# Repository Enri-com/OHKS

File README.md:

# Open-hardware knob system for acceleration control operations #

## Description

The hardware has been structured on a PCB where are mounted 9 keys and a mechanical encoder.
The keys are used to simulate, at the firmware level, the pressure of one keyboard button or a combination of them. 
Each key is equipped with anti-bounce circuitry and ade-quate ESD protection to prevent a malfunction or breakdown 
of the electronics.
The microcontroller is devoted to managing the USB HID communication. 
To have multiple options in terms of hardware solutions for the microcontroller, the PCB has been realized to be 
compatible with both ARM STM32 microcontroller and Teensy LC module.

## License

Copyright INFN-LNL 2020.
This documentation describes OHKS_WFP hardware and is licensed under the
CERN OHL v. 1.2.
You may redistribute and modify this documentation under the terms of the
CERN OHL v.1.2. (http://ohwr.org/cernohl). This documentation is distributed
WITHOUT ANY EXPRESS OR IMPLIED WARRANTY, INCLUDING OF
MERCHANTABILITY, SATISFACTORY QUALITY AND FITNESS FOR A
PARTICULAR PURPOSE. Please see the CERN OHL v.1.2 for applicable
conditions

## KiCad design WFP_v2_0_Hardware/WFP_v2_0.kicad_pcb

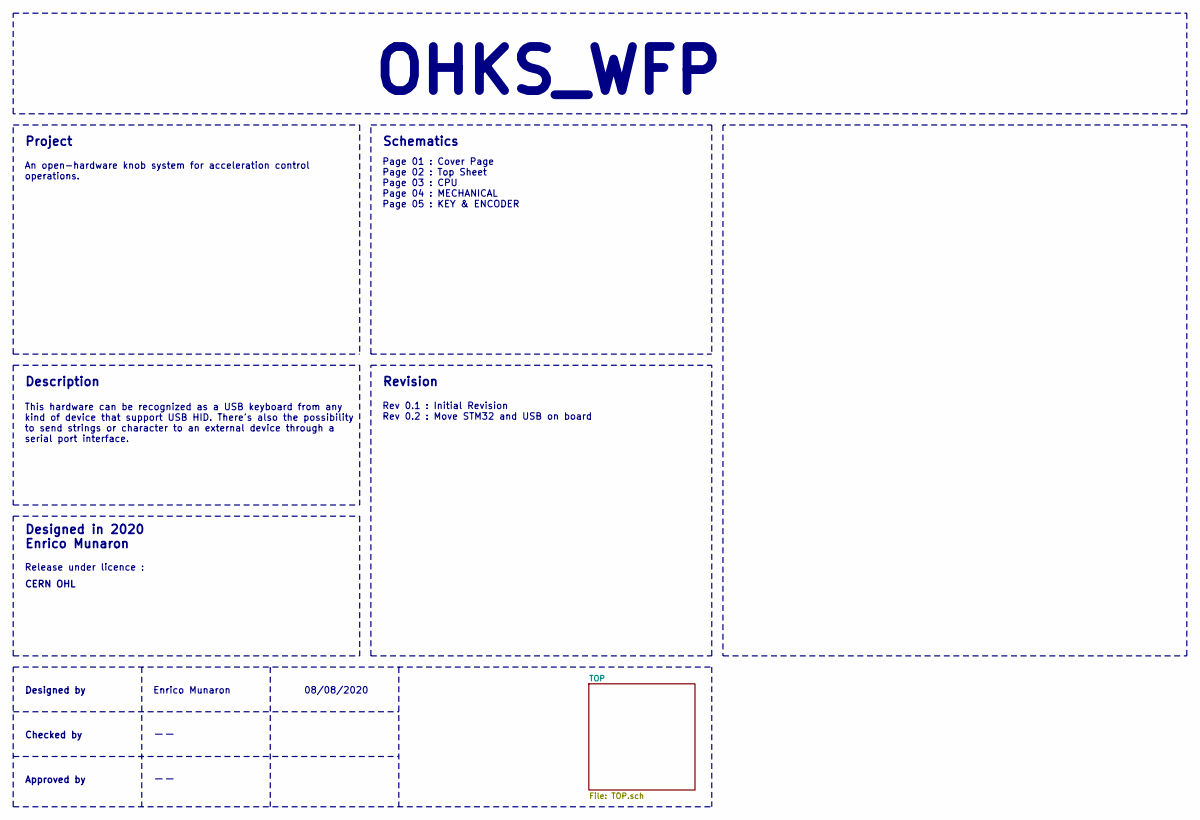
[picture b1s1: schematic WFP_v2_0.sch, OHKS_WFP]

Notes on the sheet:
OHKS_WFP
Project
Schematics
Description
Designed in 2020 Enrico Munaron
Release under licence :
CERN OHL
This hardware can be recognized as a USB keyboard from any kind of device that support USB HID. There’s also the possibility to send strings or character to an external device through a serial port interface.
An open-hardware knob system for acceleration control operations.
Page 01 : Cover Page Page 02 : Top Sheet Page 03 : CPU Page 04 : MECHANICAL Page 05 : KEY & ENCODER
Revision
Rev 0.1 : Initial Revision Rev 0.2 : Move STM32 and USB on board
Designed by
Checked by
Approved by
Enrico Munaron
08/08/2020

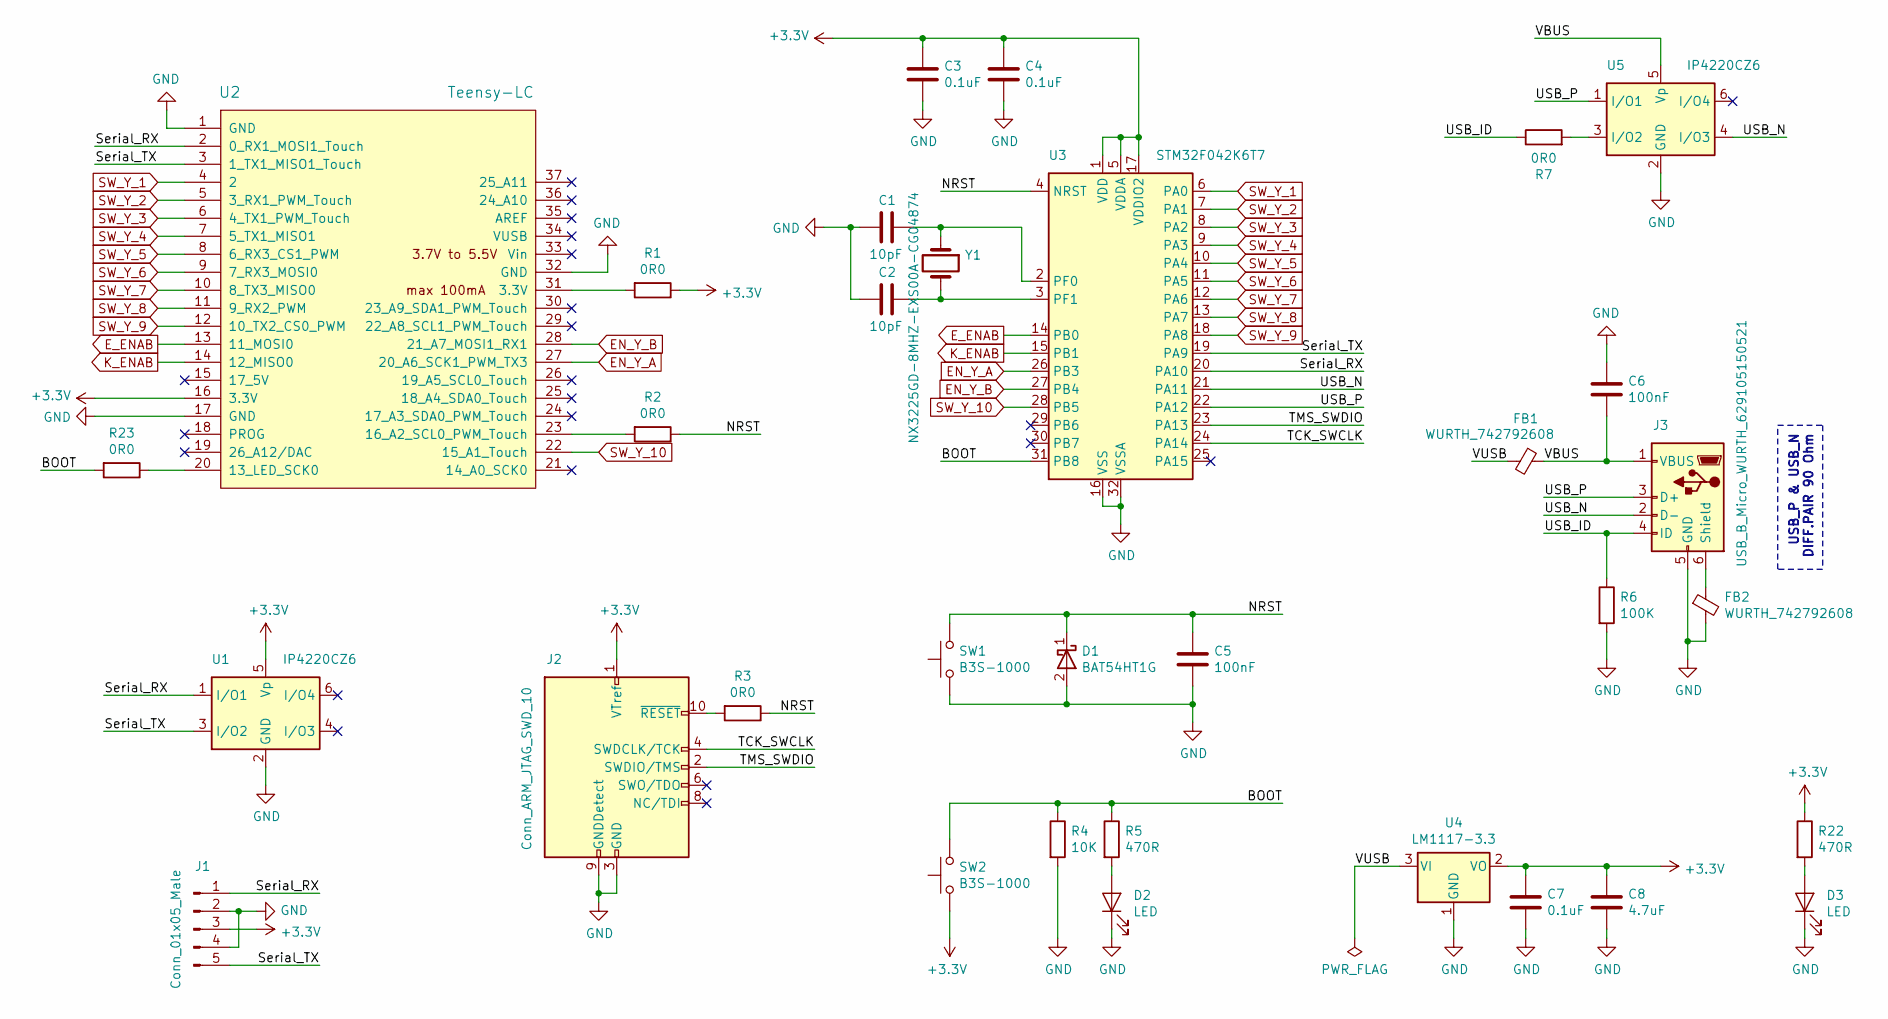
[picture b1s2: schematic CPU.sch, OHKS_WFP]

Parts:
C1, C2: 10pF; C_0603_1608Metric_Pad1.05x0.95mm_HandSolder
C3, C4, C7: 0.1uF; C_0603_1608Metric_Pad1.05x0.95mm_HandSolder
C5, C6: 100nF; C_0603_1608Metric_Pad1.05x0.95mm_HandSolder
C8: 4.7uF; C_0805_2012Metric_Pad1.15x1.40mm_HandSolder
D1: BAT54HT1G; D_SOD-323_HandSoldering
D2, D3: LED; LED_0805_2012Metric_Pad1.15x1.40mm_HandSolder
FB1, FB2: WURTH_742792608; L_0603_1608Metric_Pad1.05x0.95mm_HandSolder
J1: Conn_01x05_Male; PinHeader_1x05_P2.54mm_Vertical
J2: Conn_ARM_JTAG_SWD_10; PinHeader_2x05_P1.27mm_Vertical_SMD
J3: USB_B_Micro_WURTH_629105150521; USB_Micro-B_Wuerth_629105150521
R1, R2, R3, R7, R23: 0R0; R_0603_1608Metric_Pad1.05x0.95mm_HandSolder
R4: 10K; R_0603_1608Metric_Pad1.05x0.95mm_HandSolder
R5, R22: 470R; R_0603_1608Metric_Pad1.05x0.95mm_HandSolder
R6: 100K; R_0603_1608Metric_Pad1.05x0.95mm_HandSolder
SW1, SW2: B3S-1000; Omron_B3S-1000
U1, U5: IP4220CZ6; SOT-457
U2: Teensy-LC; Teensy_LC
U3: STM32F042K6T7; LQFP-32_7x7mm_P0.8mm
U4: LM1117-3.3; SOT-223-3_TabPin2
Y1: NX3225GD-8MHZ-EXS00A-CG04874; Crystal_SMD_3225-2Pin_3.2x2.5mm

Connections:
+3V3: C3.1, C4.1, C7.1, C8.1, J1.3, J2.1 (VTref), R1.1, R22.1, SW2.1, U1.5 (Vp), U2.16 (3.3V), U3.1 (VDD), U3.5 (VDDA), U3.17 (VDDIO2), U4.2 (VO); also elsewhere on the board
/TOP/CPU/BOOT: R4.1, R5.1, R23.2, SW2.2, U3.31 (PB8)
/TOP/CPU/NRST: C5.1, D1.1 (K), R2.1, R3.1, SW1.2, U3.4 (NRST)
/TOP/CPU/Serial_RX: J1.1, U1.1 (I/O1), U2.2 (0_RX1_MOSI1_Touch), U3.20 (PA10)
/TOP/CPU/Serial_TX: J1.5, U1.3 (I/O2), U2.3 (1_TX1_MISO1_Touch), U3.19 (PA9)
/TOP/CPU/TCK_SWCLK: J2.4 (SWDCLK/TCK), U3.24 (PA14)
/TOP/CPU/TMS_SWDIO: J2.2 (SWDIO/TMS), U3.23 (PA13)
/TOP/CPU/USB_ID: J3.4 (ID), R6.1, R7.1
/TOP/CPU/USB_N: J3.2 (D-), U3.21 (PA11), U5.4 (I/O3)
/TOP/CPU/USB_P: J3.3 (D+), U3.22 (PA12), U5.1 (I/O1)
/TOP/CPU/VBUS: C6.2, FB1.1, J3.1 (VBUS), U5.5 (Vp)
/TOP/CPU/VUSB: FB1.2, U4.3 (VI)
EN_Y_A: U2.27 (20_A6_SCK1_PWM_TX3), U3.26 (PB3); also elsewhere on the board
EN_Y_B: U2.28 (21_A7_MOSI1_RX1), U3.27 (PB4); also elsewhere on the board
E_ENAB: U2.13 (11_MOSI0), U3.14 (PB0); also elsewhere on the board
GND: C1.2, C2.2, C3.2, C4.2, C5.2, C6.1, C7.2, C8.2, D1.2 (A), D2.1 (K), D3.1 (K), FB2.2, J1.2, J1.4, J2.3 (GND), J2.5 (GND), J2.9 (GNDDetect), J3.5 (GND), R4.2, R6.2, SW1.1, U1.2 (GND), U2.1 (GND), U2.17 (GND), U2.32 (GND), U3.16 (VSS), U3.32 (VSSA), U4.1 (GND), U5.2 (GND); also elsewhere on the board
K_ENAB: U2.14 (12_MISO0), U3.15 (PB1); also elsewhere on the board
unnamed: C1.1, U3.2 (PF0), Y1.1
unnamed: C2.1, U3.3 (PF1), Y1.2
unnamed: D2.2 (A), R5.2
unnamed: D3.2 (A), R22.2
unnamed: FB2.1, J3.6 (Shield)
unnamed: J2.10 (~RESET~), R3.2
unnamed: R1.2, U2.31 (3.3V)
unnamed: R2.2, U2.23 (16_A2_SCL0_PWM_Touch)
unnamed: R7.2, U5.3 (I/O2)
unnamed: R23.1, U2.20 (13_LED_SCK0)
SW_Y_1: U2.4 (2), U3.6 (PA0); also elsewhere on the board
SW_Y_2: U2.5 (3_RX1_PWM_Touch), U3.7 (PA1); also elsewhere on the board
SW_Y_3: U2.6 (4_TX1_PWM_Touch), U3.8 (PA2); also elsewhere on the board
SW_Y_4: U2.7 (5_TX1_MISO1), U3.9 (PA3); also elsewhere on the board
SW_Y_5: U2.8 (6_RX3_CS1_PWM), U3.10 (PA4); also elsewhere on the board
SW_Y_6: U2.9 (7_RX3_MOSI0), U3.11 (PA5); also elsewhere on the board
SW_Y_7: U2.10 (8_TX3_MISO0), U3.12 (PA6); also elsewhere on the board
SW_Y_8: U2.11 (9_RX2_PWM), U3.13 (PA7); also elsewhere on the board
SW_Y_9: U2.12 (10_TX2_CS0_PWM), U3.18 (PA8); also elsewhere on the board
SW_Y_10: U2.22 (15_A1_Touch), U3.28 (PB5); also elsewhere on the board

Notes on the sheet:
USB_P & USB_N DIFF.PAIR 90 Ohm

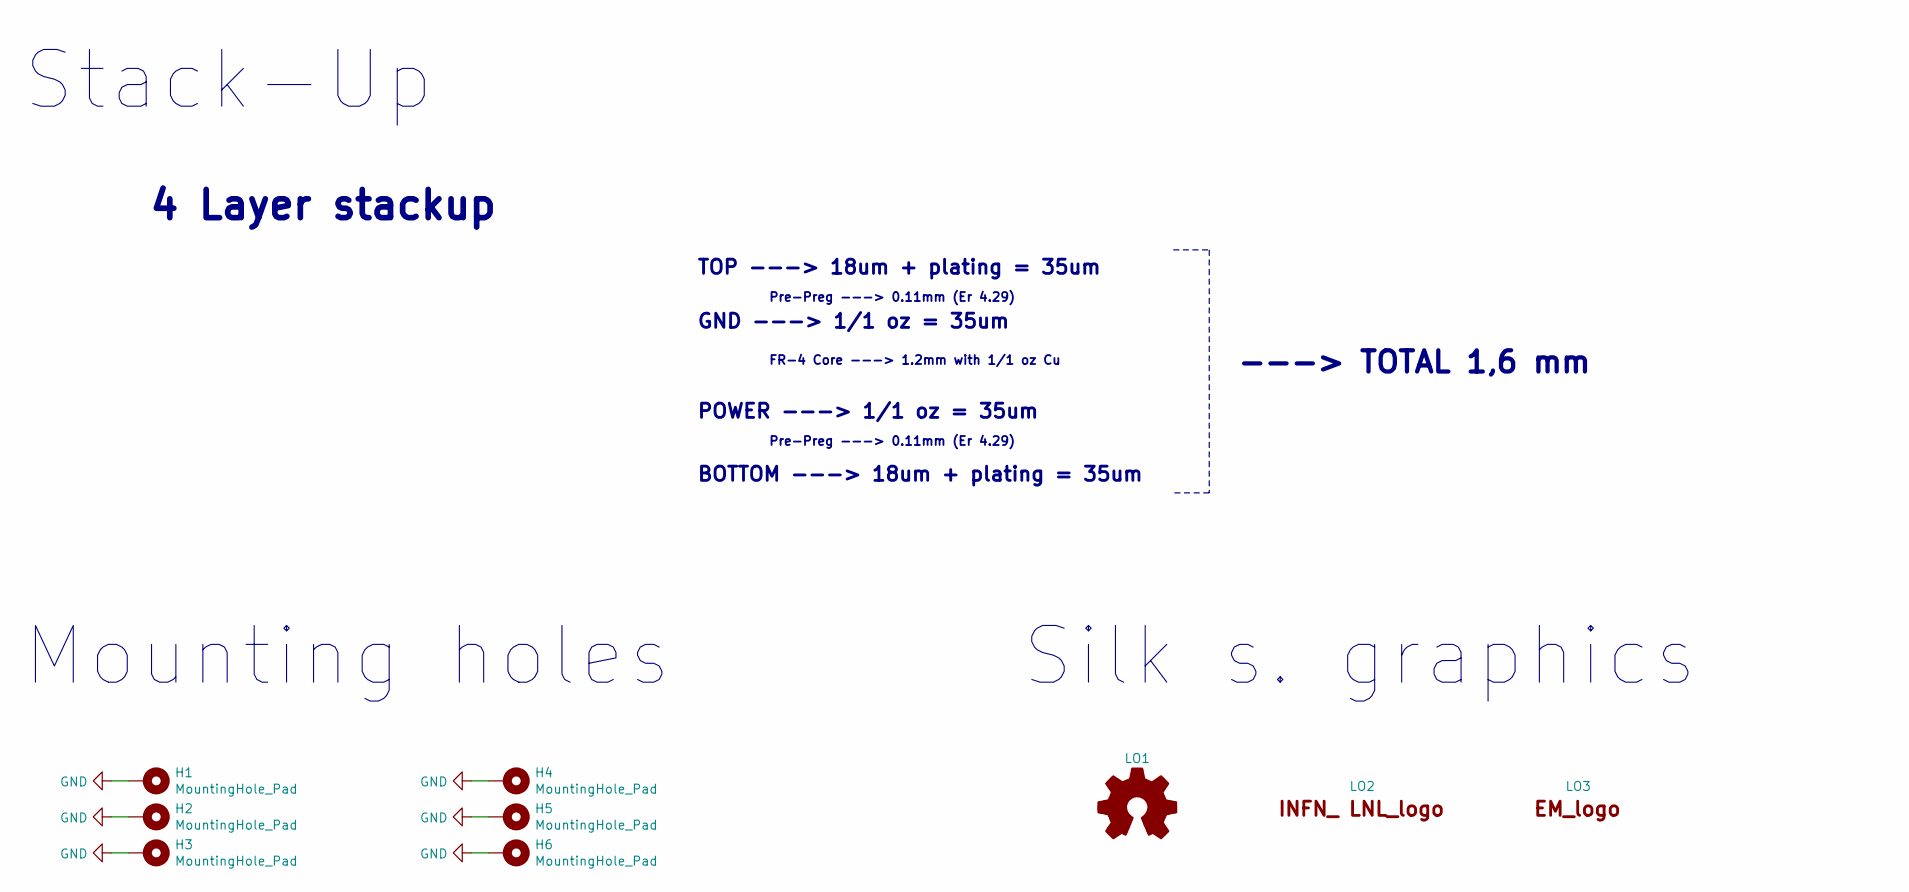
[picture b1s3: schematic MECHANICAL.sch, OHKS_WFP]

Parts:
H1, H2, H3, H4, H5, H6: MountingHole_Pad; MountingHole_3.2mm_M3_Pad_Via
LO1: Logo_Open_Hardware_Small; OSHW-Logo_5.7x6mm_SilkScreen
LO2: Logo_INFN_LNL; INFN_LNL_Logo
LO3: Logo_EM; EM_Logo_13x9

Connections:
GND: H1.1, H2.1, H3.1, H4.1, H5.1, H6.1; also elsewhere on the board

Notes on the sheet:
Pre-Preg ---> 0.11mm (Er 4.29)
TOP ---> 18um + plating = 35um
GND ---> 1/1 oz = 35um
POWER ---> 1/1 oz = 35um
BOTTOM ---> 18um + plating = 35um
FR-4 Core ---> 1.2mm with 1/1 oz Cu
4 Layer stackup
Stack-Up
Mounting holes
Silk s. graphics
---> TOTAL 1,6 mm

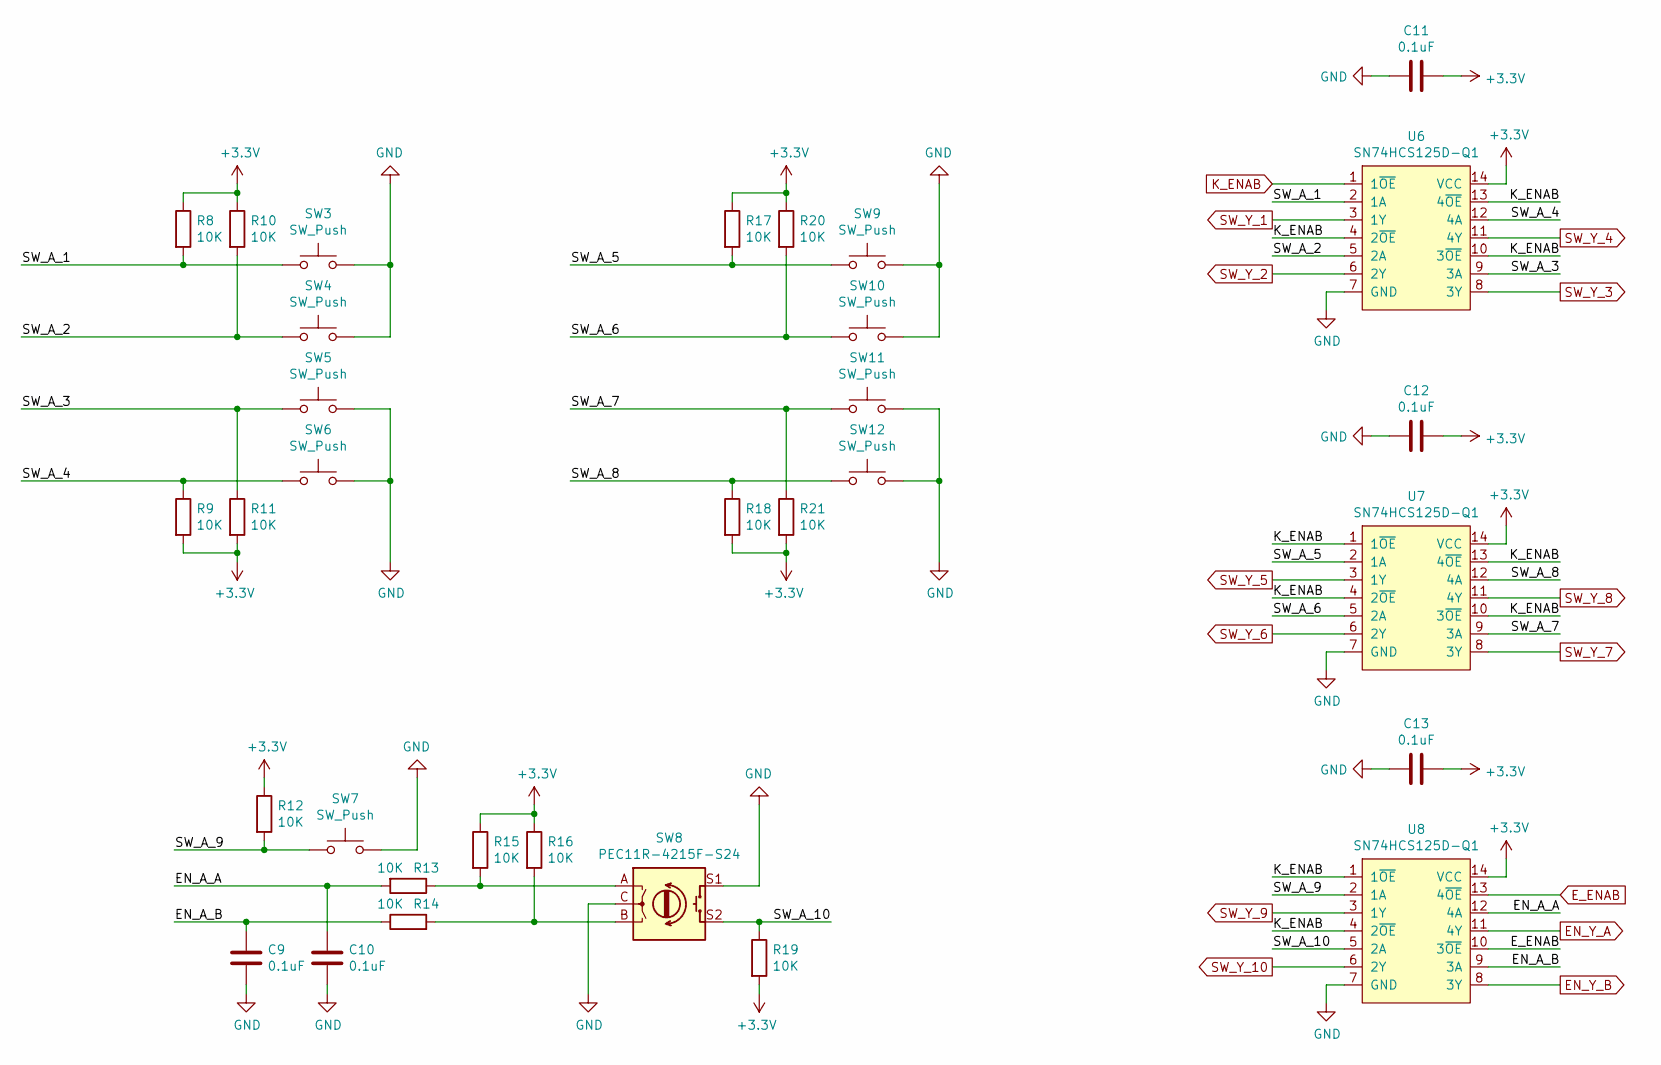
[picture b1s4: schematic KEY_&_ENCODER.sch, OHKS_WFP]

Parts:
C9, C10, C11, C12, C13: 0.1uF; C_0603_1608Metric_Pad1.05x0.95mm_HandSolder
R8, R9, R10, R11, R12, R13, R14, R15, R16, R17, R18, R19, R20, R21: 10K; R_0603_1608Metric_Pad1.05x0.95mm_HandSolder
SW3, SW4, SW5, SW6, SW7, SW9, SW10, SW11, SW12: SW_Push; SW_Cherry_MX_1.00u_PCB
SW8: PEC11R-4215F-S24; PEC11R
U6, U7, U8: SN74HCS125D-Q1; SOIC-14_3.9x8.7mm_P1.27mm

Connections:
+3V3: C11.1, C12.1, C13.1, R8.1, R9.2, R10.1, R11.2, R12.1, R15.1, R16.1, R17.1, R18.2, R19.2, R20.1, R21.2, U6.14 (VCC), U7.14 (VCC), U8.14 (VCC); also elsewhere on the board
/TOP/KEY & ENCODER/EN_A_A: C10.1, R13.2, U8.12 (4A)
/TOP/KEY & ENCODER/EN_A_B: C9.1, R14.1, U8.9 (3A)
/TOP/KEY & ENCODER/SW_A_1: R8.2, SW3.1, U6.2 (1A)
/TOP/KEY & ENCODER/SW_A_2: R10.2, SW4.1, U6.5 (2A)
/TOP/KEY & ENCODER/SW_A_3: R11.1, SW5.1, U6.9 (3A)
/TOP/KEY & ENCODER/SW_A_4: R9.1, SW6.1, U6.12 (4A)
/TOP/KEY & ENCODER/SW_A_5: R17.2, SW9.1, U7.2 (1A)
/TOP/KEY & ENCODER/SW_A_6: R20.2, SW10.1, U7.5 (2A)
/TOP/KEY & ENCODER/SW_A_7: R21.1, SW11.1, U7.9 (3A)
/TOP/KEY & ENCODER/SW_A_8: R18.1, SW12.1, U7.12 (4A)
/TOP/KEY & ENCODER/SW_A_9: R12.2, SW7.1, U8.2 (1A)
/TOP/KEY & ENCODER/SW_A_10: R19.1, SW8.S2, U8.5 (2A)
EN_Y_A: U8.11 (4Y); also elsewhere on the board
EN_Y_B: U8.8 (3Y); also elsewhere on the board
E_ENAB: U8.10 (3~OE), U8.13 (4~OE); also elsewhere on the board
GND: C9.2, C10.2, C11.2, C12.2, C13.2, SW3.2, SW4.2, SW5.2, SW6.2, SW7.2, SW8.C, SW8.S1, SW9.2, SW10.2, SW11.2, SW12.2, U6.7 (GND), U7.7 (GND), U8.7 (GND); also elsewhere on the board
K_ENAB: U6.1 (1~OE), U6.4 (2~OE), U6.10 (3~OE), U6.13 (4~OE), U7.1 (1~OE), U7.4 (2~OE), U7.10 (3~OE), U7.13 (4~OE), U8.1 (1~OE), U8.4 (2~OE); also elsewhere on the board
unnamed: R13.1, R15.2, SW8.A
unnamed: R14.2, R16.2, SW8.B
SW_Y_1: U6.3 (1Y); also elsewhere on the board
SW_Y_2: U6.6 (2Y); also elsewhere on the board
SW_Y_3: U6.8 (3Y); also elsewhere on the board
SW_Y_4: U6.11 (4Y); also elsewhere on the board
SW_Y_5: U7.3 (1Y); also elsewhere on the board
SW_Y_6: U7.6 (2Y); also elsewhere on the board
SW_Y_7: U7.8 (3Y); also elsewhere on the board
SW_Y_8: U7.11 (4Y); also elsewhere on the board
SW_Y_9: U8.3 (1Y); also elsewhere on the board
SW_Y_10: U8.6 (2Y); also elsewhere on the board

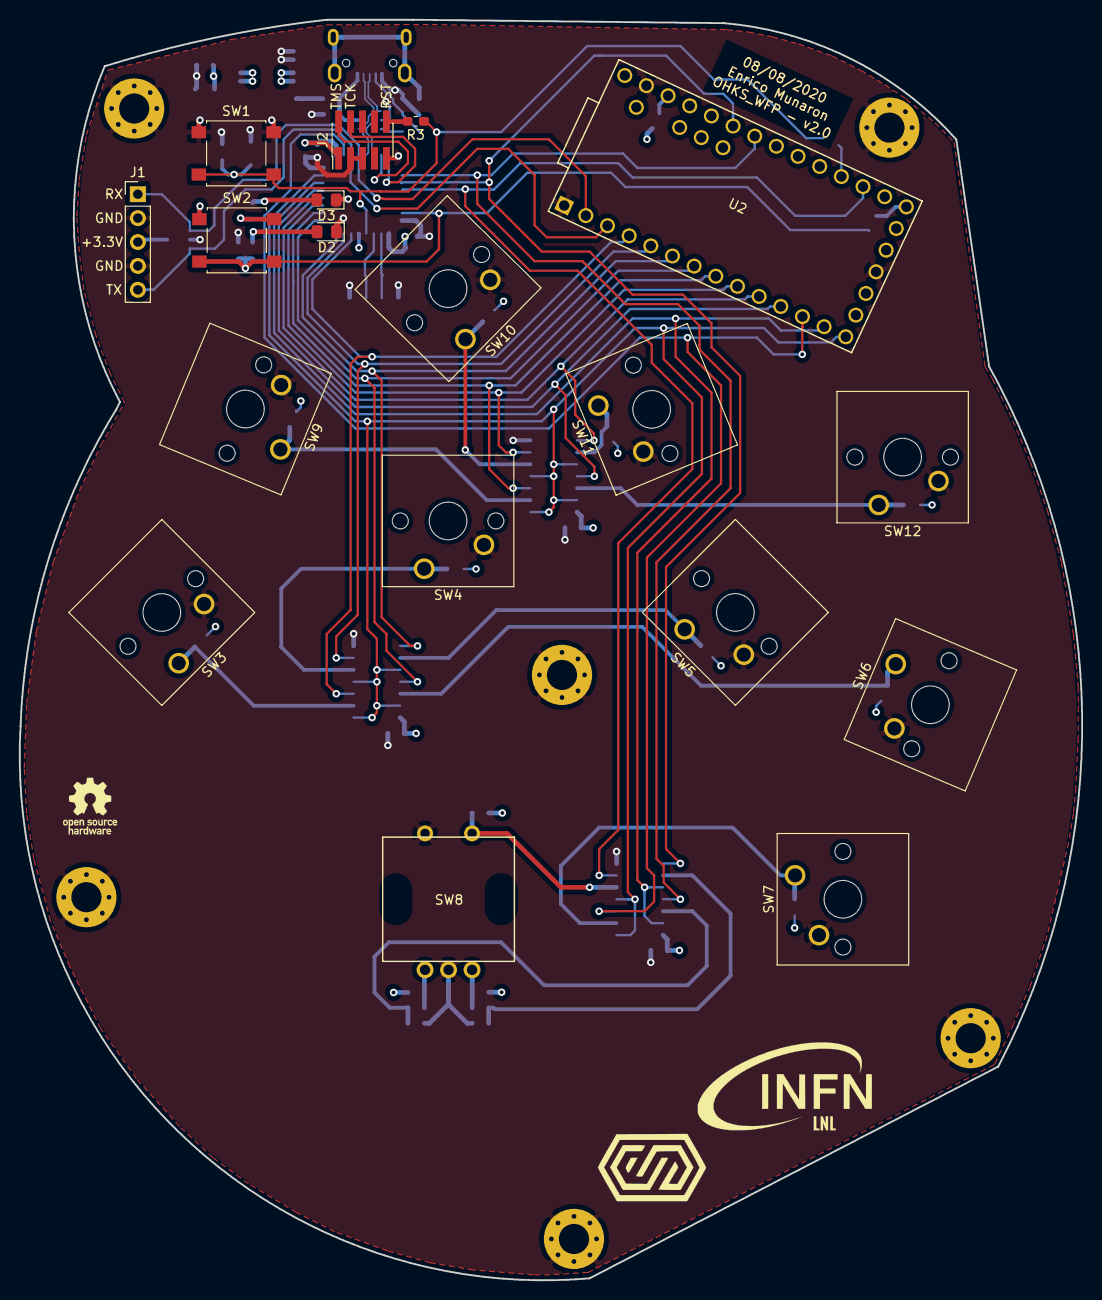
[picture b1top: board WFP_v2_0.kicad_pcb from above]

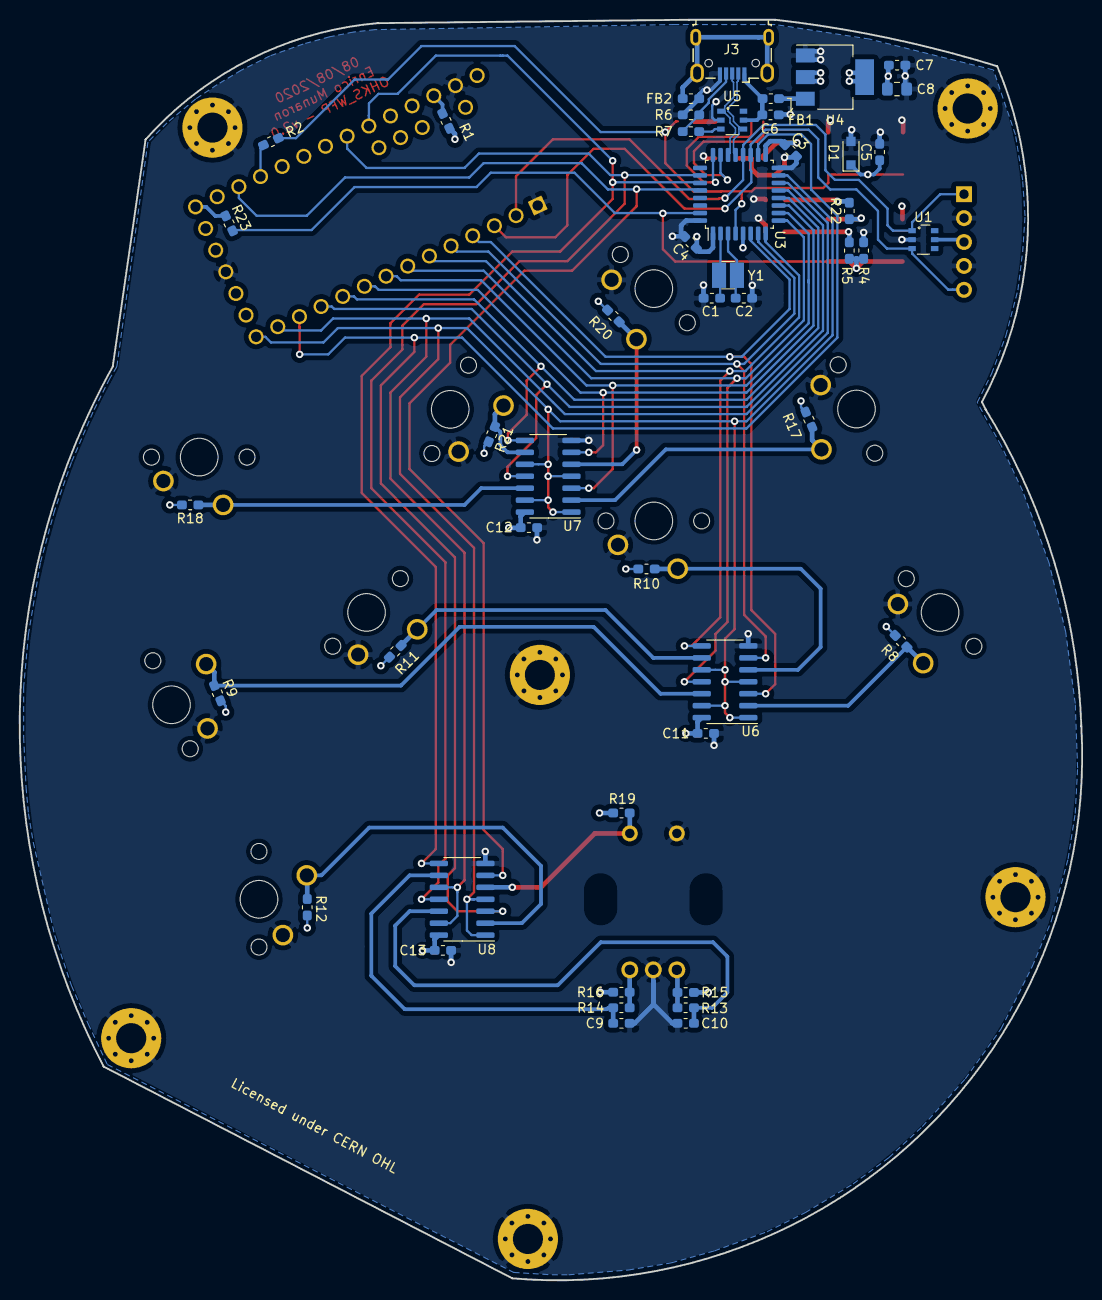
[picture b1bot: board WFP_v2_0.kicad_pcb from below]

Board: 4 copper layers, 112.9 x 134.0 mm, 74 parts (47 on the bottom side), 51 nets.

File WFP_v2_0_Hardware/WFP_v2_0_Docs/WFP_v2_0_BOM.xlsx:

Qty: | Reference(s): | Value: | Part number: | Manufacturer:
2 | C1, C2 | 10pF | 0603 10pF C0G | GENERIC
10 | C3, C4,C5, C6, C7, C9, C10, C11, C12, C13 | 0.1uF | 0603 100nF X7R | GENERIC
1 | C8 | 4.7uF | 0805 4.7uF not polarized multilayer | GENERIC
1 | D1 | BAT54HT1G | BAT54HT1G | ONSEMI
2 | D2, D3 | LED | 0805 Green LED | GENERIC
2 | FB1, FB2 | WURTH_742792608 | 742792608 | WURTH
1 | J1 | Conn_01x05_Male | Connector:Conn_01x05_Male | GENERIC
1 | J2 | Conn_ARM_JTAG_SWD_10 | Connector:Conn_ARM_JTAG_SWD_10 | GENERIC
1 | J3 | USB_B_Micro_WURTH_629105150521 | 629105150521 | WURTH
4 | R1, R2, R3, R7, R23 | 0R0 | 0603 0R0 | GENERIC
15 | R4, R8, R9, R10, R11, R12, R13, R14, R15, R16, R17, R18, R19, R20, R21 | 10K | 0603 10K | GENERIC
2 | R5, R22 | 470R | 0603 470R | GENERIC
1 | R6 | 100K | 0603 100K | GENERIC
2 | SW1, SW2 | B3S-1000 | B3S-1000 | OMRON
9 | SW3, SW4, SW5, SW6, SW7, SW9, SW10, SW11, SW12 | SW_Push | MX1A-11NW | ZF
1 | SW8 | PEC11R-4215F-S24 | PEC11R-4215F-S24 | BOURNS
2 | U1, U5 | IP4220CZ6 | IP4220CZ6 | NEXPERIA
1 | U2 | Teensy-LC | Teensy-LC | PJRC
1 | U3 | STM32F042K6T7 | STM32F042K6T7 | STMICROELECTRONICS
1 | U4 | LM1117-3.3 | LM1117IMP-3.3/NOPB | TI
3 | U6, U7, U8 | SN74HCS125D-Q1 | SN74HCS125-Q | TI
1 | Y1 | NX3225GD-8MHZ-EXS00A-CG04874 | NX3225GD-8MHZ-STD-CRA-3 | NDK

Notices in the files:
WFP_v2_0_Hardware/WFP_v2_0.kicad_pcb:
Licensed under CERN OHL
